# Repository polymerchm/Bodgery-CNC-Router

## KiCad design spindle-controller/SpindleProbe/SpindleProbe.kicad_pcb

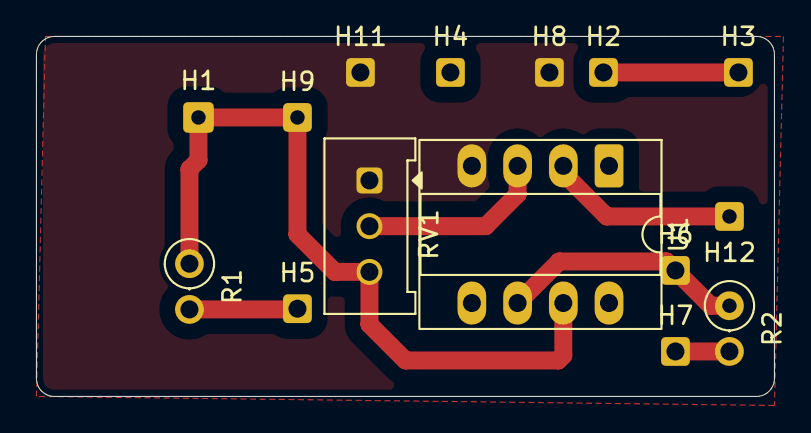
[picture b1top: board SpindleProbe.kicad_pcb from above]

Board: 2 copper layers, 41.0 x 20.0 mm, 15 parts (0 on the bottom side), 8 nets.

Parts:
H1: MountingHole_Pad; SolderWire-0.15sqmm_1x01_D0.5mm_OD1.5mm
H2, H3, H4, H5, H6, H7, H8, H9, H11, H12: MountingHole_Pad; SolderWire-0.1sqmm_1x01_D0.4mm_OD1mm
R1, R2: 330 ohm; R_Axial_DIN0207_L6.3mm_D2.5mm_P2.54mm_Vertical
RV1: R_Potentiometer_Trim; Potentiometer_Bourns_3386W_Horizontal
U1: LM741; CERDIP-8_W7.62mm_SideBrazed_LongPads_Socket

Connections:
/GND: H3.1 (1_1), H8.1 (1_1), H11.1 (1_1), RV1.1, U1.4 (V-)
/VCC: H1.1 (1_1), H9.1 (1_1), R1.1, RV1.3, U1.7 (V+)
unnamed: H2.1 (1_1), H4.1 (1_1)
unnamed: H5.1 (1_1), R1.2
unnamed: H6.1 (1_1), R2.1, U1.6
unnamed: H7.1 (1_1), R2.2
unnamed: RV1.2, U1.3 (+)
unnamed: H12.1 (1_1), U1.2 (-)
